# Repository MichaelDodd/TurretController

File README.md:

# TurretController
Private project for turret control

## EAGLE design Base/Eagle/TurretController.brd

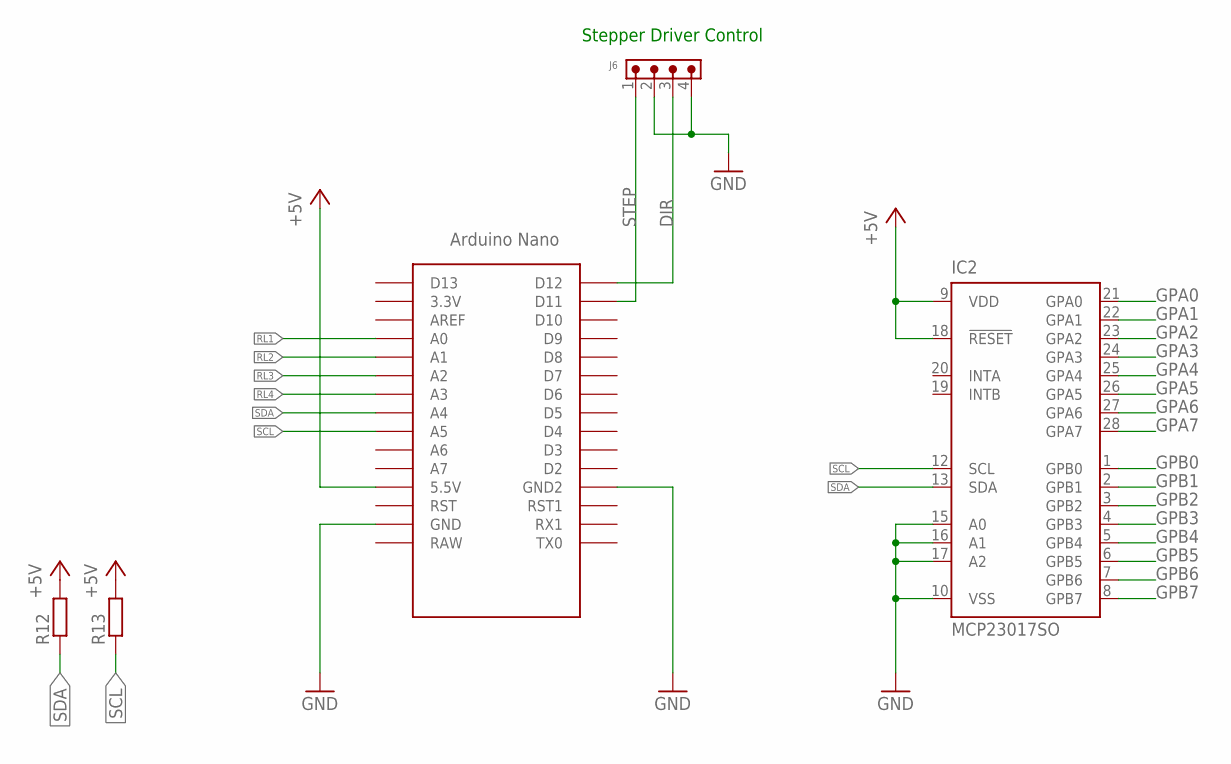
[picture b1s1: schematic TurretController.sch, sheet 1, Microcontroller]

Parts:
IC2: MCP23017SO; SO28W
J6: 691305330004
R12, R13: R-EU_R0805; R0805
U$1: NANO

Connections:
+5V: IC2.9 (VDD), IC2.18 (!RESET), R12.2, R13.2, U$1.5V (5.5V); also elsewhere on the board
DIR: J6.3, U$1.D12
GND: IC2.10 (VSS), IC2.15 (A0), IC2.16 (A1), IC2.17 (A2), J6.2, J6.4, U$1.GND, U$1.GND1 (GND2); also elsewhere on the board
GPA0: IC2.21 (GPA0); also elsewhere on the board
GPA1: IC2.22 (GPA1); also elsewhere on the board
GPA2: IC2.23 (GPA2); also elsewhere on the board
GPA3: IC2.24 (GPA3); also elsewhere on the board
GPA4: IC2.25 (GPA4); also elsewhere on the board
GPA5: IC2.26 (GPA5); also elsewhere on the board
GPA6: IC2.27 (GPA6); also elsewhere on the board
GPA7: IC2.28 (GPA7); also elsewhere on the board
GPB0: IC2.1 (GPB0); also elsewhere on the board
GPB1: IC2.2 (GPB1); also elsewhere on the board
GPB2: IC2.3 (GPB2); also elsewhere on the board
GPB3: IC2.4 (GPB3); also elsewhere on the board
GPB4: IC2.5 (GPB4); also elsewhere on the board
GPB5: IC2.6 (GPB5); also elsewhere on the board
GPB6: IC2.7 (GPB6); also elsewhere on the board
GPB7: IC2.8 (GPB7); also elsewhere on the board
RL1: U$1.A0; also elsewhere on the board
RL2: U$1.A1; also elsewhere on the board
RL3: U$1.A2; also elsewhere on the board
RL4: U$1.A3; also elsewhere on the board
SCL: IC2.12 (SCL), R13.1, U$1.A5
SDA: IC2.13 (SDA), R12.1, U$1.A4
STEP: J6.1, U$1.D11

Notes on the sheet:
Stepper Driver Control

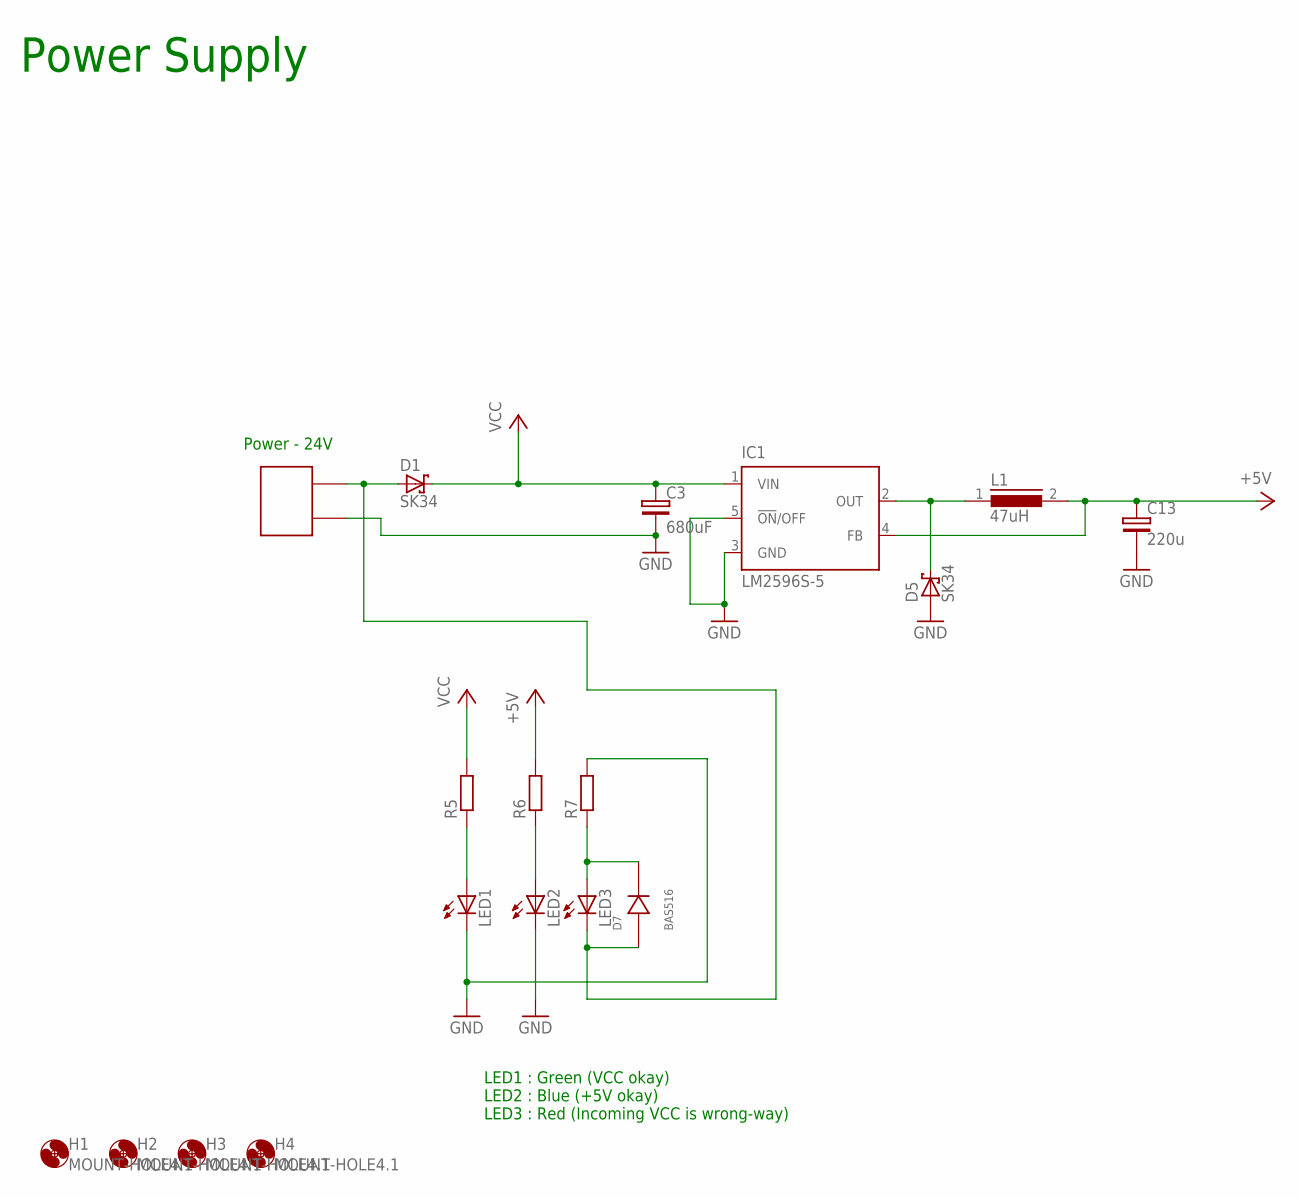
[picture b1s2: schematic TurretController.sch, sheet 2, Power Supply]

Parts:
C3: 680uF; C8.15X4X16.5
C13: 220u; PAN-PTH-8X11X3.5
CN1: 2EDG-2
D1, D5: SK34; DO214AC
D7: BAS516; SOD523
H1, H2, H3, H4: MOUNT-HOLE4.1; 4,1
IC1: LM2596S-5; TO263-5
L1: 47uH; B82476A1
LED1, LED2, LED3: LEDCHIPLED_0805; CHIPLED_0805
R5, R6, R7: R-EU_R0805; R0805

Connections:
+5V: C13.+, IC1.4 (FB), L1.2, R6.2; also elsewhere on the board
GND: C3.-, C13.-, CN1.P$1, D5.A, IC1.3 (GND), IC1.5 (!ON!/OFF), LED1.C, LED2.C, R7.2; also elsewhere on the board
unnamed: D7.C (K), LED3.A, R7.1
unnamed: D5.C, IC1.2 (OUT), L1.1
unnamed: CN1.P$2, D1.A, D7.A, LED3.C
unnamed: LED1.A, R5.1
unnamed: LED2.A, R6.1
VCC: C3.+, D1.C, IC1.1 (VIN), R5.2; also elsewhere on the board

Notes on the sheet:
LED1 : Green (VCC okay) LED2 : Blue (+5V okay) LED3 : Red (Incoming VCC is wrong-way)
Power Supply
Power - 24V

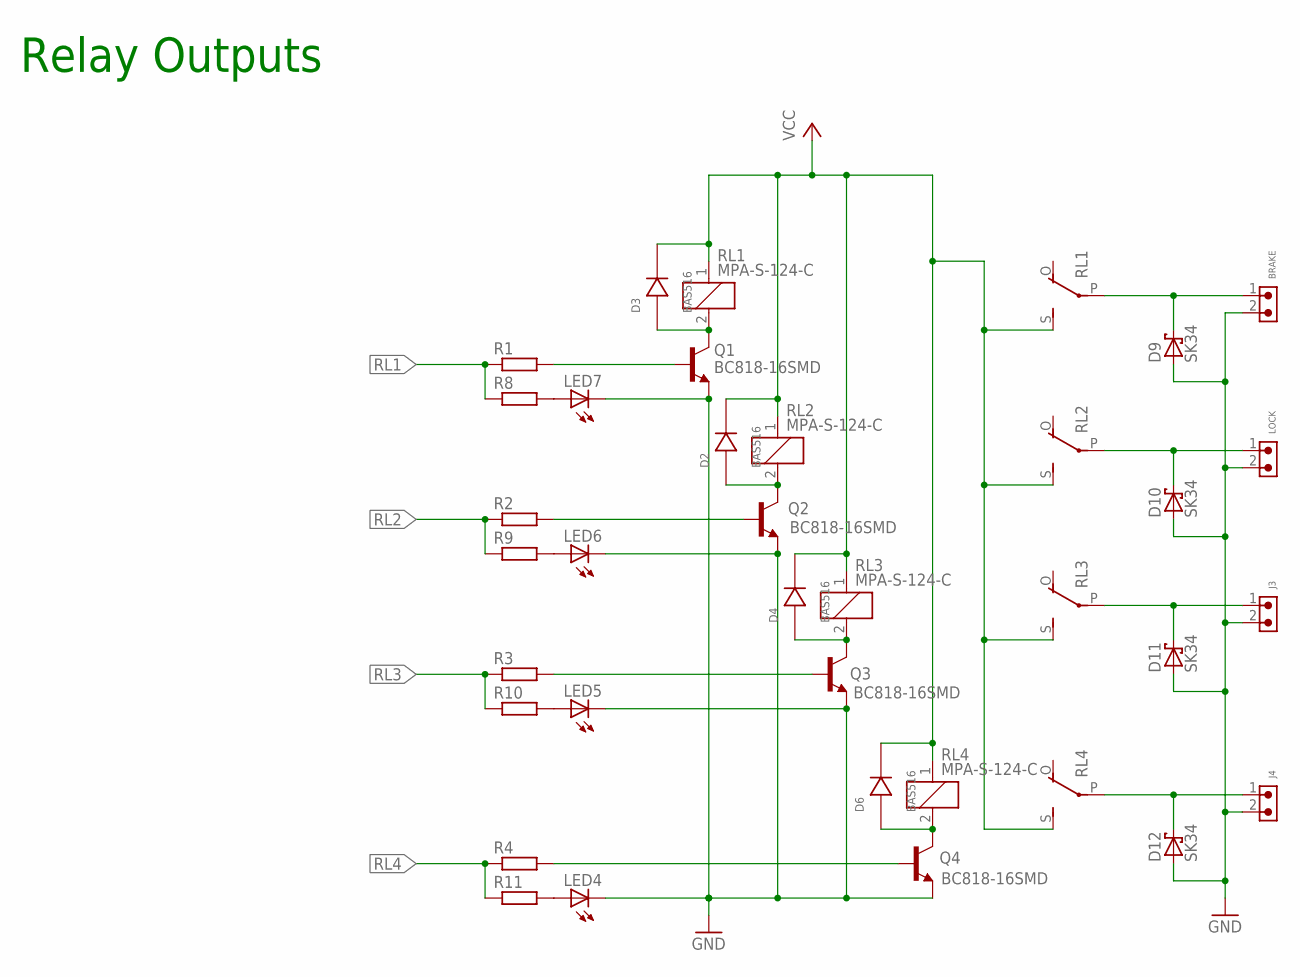
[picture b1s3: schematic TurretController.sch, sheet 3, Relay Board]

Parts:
BRAKE: 691305330002
D2, D3, D4, D6: BAS516; SOD523
D9, D10, D11, D12: SK34; DO214AC
J3, J4: 691305330002
LED4, LED5, LED6, LED7: LEDCHIPLED_0805; CHIPLED_0805
LOCK: 691305330002
Q1, Q2, Q3, Q4: BC818-16SMD; SOT23-BEC
R1, R2, R3, R4, R8, R9, R10, R11: R-EU_R0805; R0805
RL1, RL2, RL3, RL4: MPA-S-124-C; G5LE

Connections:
GND: BRAKE.2, D9.A, D10.A, D11.A, D12.A, J3.2, J4.2, LED4.C, LED5.C, LED6.C, LED7.C, LOCK.2, Q1.E, Q2.E, Q3.E, Q4.E; also elsewhere on the board
unnamed: D12.C, J4.1, RL4.P
unnamed: D11.C, J3.1, RL3.P
unnamed: D10.C, LOCK.1, RL2.P
unnamed: BRAKE.1, D9.C, RL1.P
unnamed: D2.A, Q2.C, RL2.2
unnamed: LED4.A, R11.2
unnamed: D4.A, Q3.C, RL3.2
unnamed: D3.A, Q1.C, RL1.2
unnamed: D6.A, Q4.C, RL4.2
unnamed: Q1.B, R1.2
unnamed: Q2.B, R2.2
unnamed: Q3.B, R3.2
unnamed: Q4.B, R4.2
unnamed: LED5.A, R10.2
unnamed: LED6.A, R9.2
unnamed: LED7.A, R8.2
RL1: R1.1, R8.1; also elsewhere on the board
RL2: R2.1, R9.1; also elsewhere on the board
RL3: R3.1, R10.1; also elsewhere on the board
RL4: R4.1, R11.1; also elsewhere on the board
VCC: D2.C (K), D3.C (K), D4.C (K), D6.C (K), RL1.1, RL1.S, RL2.1, RL2.S, RL3.1, RL3.S, RL4.1, RL4.S; also elsewhere on the board

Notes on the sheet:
Relay Outputs

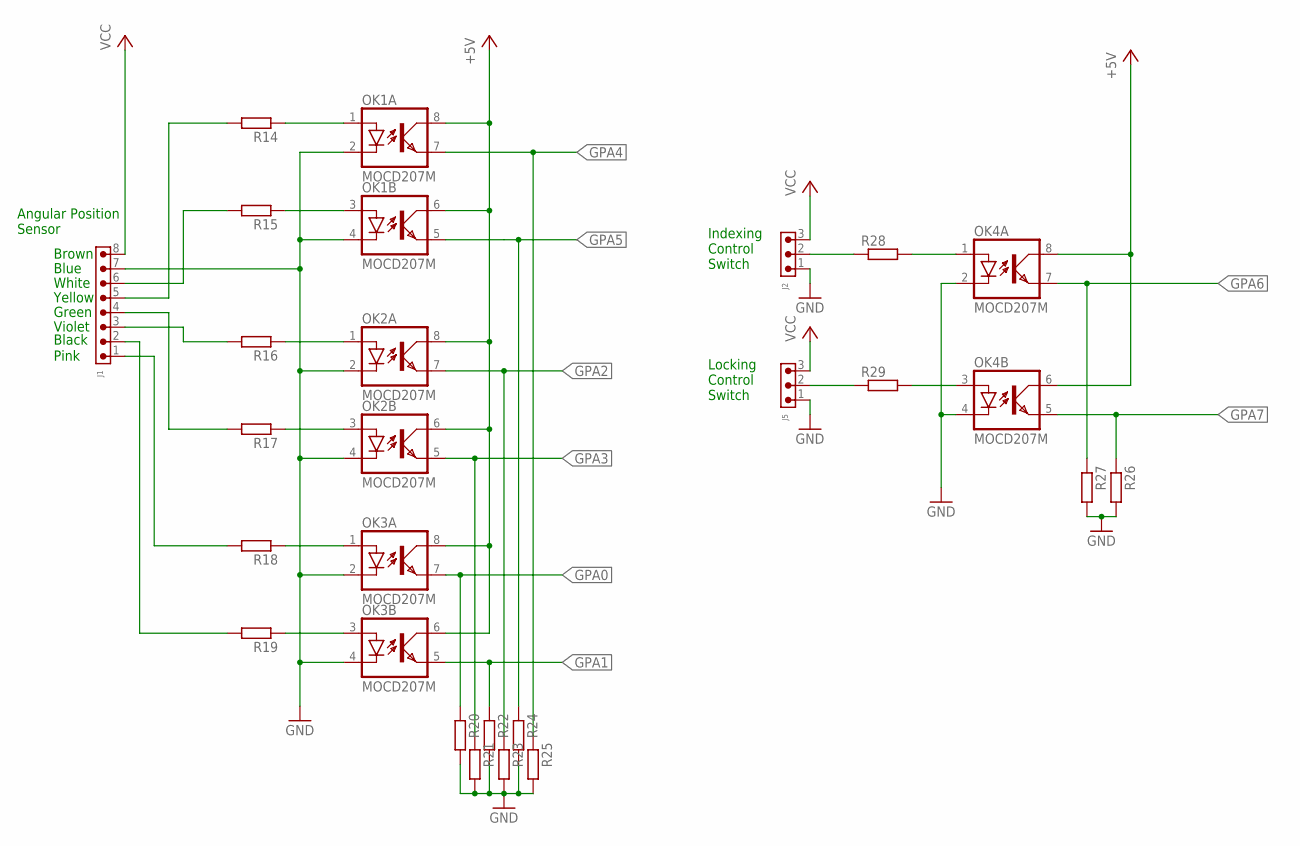
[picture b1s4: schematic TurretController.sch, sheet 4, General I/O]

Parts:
J1: 691305330008
J2, J5: 691305330003
OK1, OK2, OK3, OK4: MOCD207M; SOIC08-FAIRCHILD
R14, R15, R16, R17, R18, R19, R20, R21, R22, R23, R24, R25, R26, R27, R28, R29: R-EU_R0805; R0805

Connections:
+5V: OK1.6 (COL), OK1.8 (COL), OK2.6 (COL), OK2.8 (COL), OK3.6 (COL), OK3.8 (COL), OK4.6 (COL), OK4.8 (COL); also elsewhere on the board
GND: J1.7, J2.1, J5.1, OK1.2 (C), OK1.4 (C), OK2.2 (C), OK2.4 (C), OK3.2 (C), OK3.4 (C), OK4.2 (C), OK4.4 (C), R20.2, R21.2, R22.2, R23.2, R24.2, R25.2, R26.2, R27.2; also elsewhere on the board
GPA0: OK3.7 (EMIT), R20.1; also elsewhere on the board
GPA1: OK3.5 (EMIT), R22.1; also elsewhere on the board
GPA2: OK2.7 (EMIT), R23.1; also elsewhere on the board
GPA3: OK2.5 (EMIT), R21.1; also elsewhere on the board
GPA4: OK1.7 (EMIT), R25.1; also elsewhere on the board
GPA5: OK1.5 (EMIT), R24.1; also elsewhere on the board
GPA6: OK4.7 (EMIT), R27.1; also elsewhere on the board
GPA7: OK4.5 (EMIT), R26.1; also elsewhere on the board
unnamed: J1.1, R18.2
unnamed: J2.2, R28.1
unnamed: OK4.1 (A), R28.2
unnamed: OK4.3 (A), R29.2
unnamed: J5.2, R29.1
unnamed: J1.3, R16.2
unnamed: J1.4, R17.2
unnamed: J1.6, R15.2
unnamed: J1.5, R14.2
unnamed: OK2.3 (A), R17.1
unnamed: OK1.1 (A), R14.1
unnamed: OK1.3 (A), R15.1
unnamed: OK2.1 (A), R16.1
unnamed: OK3.1 (A), R18.1
unnamed: OK3.3 (A), R19.1
unnamed: J1.2, R19.2
VCC: J1.8, J2.3, J5.3; also elsewhere on the board

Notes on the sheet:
Angular Position Sensor
Indexing Control Switch
Locking Control Switch
Brown
Blue
White
Yellow
Green
Violet
Black
Pink

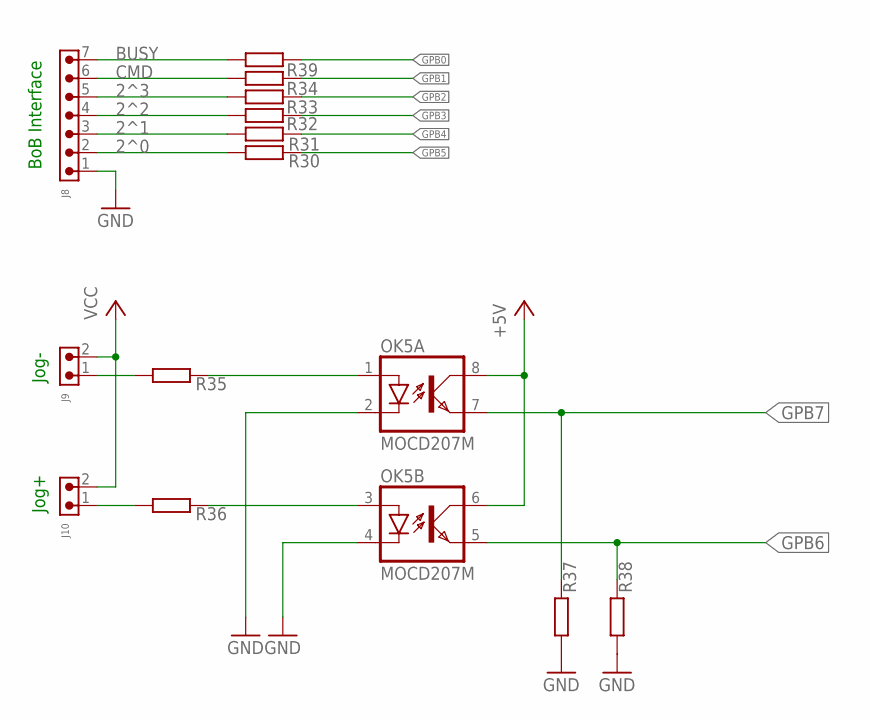
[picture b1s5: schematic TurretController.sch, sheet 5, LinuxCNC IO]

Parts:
J8: 691305330007
J9, J10: 691305330002
OK5: MOCD207M; SOIC08-FAIRCHILD
R30, R31, R32, R33, R34, R35, R36, R37, R38, R39: R-EU_R0805; R0805

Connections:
2^0: J8.2, R30.2
2^1: J8.3, R31.2
2^2: J8.4, R32.2
2^3: J8.5, R33.2
+5V: OK5.6 (COL), OK5.8 (COL); also elsewhere on the board
BUSY: J8.7, R39.2
CMD: J8.6, R34.2
GND: J8.1, OK5.2 (C), OK5.4 (C), R37.2, R38.2; also elsewhere on the board
GPB0: R39.1; also elsewhere on the board
GPB1: R34.1; also elsewhere on the board
GPB2: R33.1; also elsewhere on the board
GPB3: R32.1; also elsewhere on the board
GPB4: R31.1; also elsewhere on the board
GPB5: R30.1; also elsewhere on the board
GPB6: OK5.5 (EMIT), R38.1; also elsewhere on the board
GPB7: OK5.7 (EMIT), R37.1; also elsewhere on the board
unnamed: J9.1, R35.2
unnamed: J10.1, R36.2
unnamed: OK5.3 (A), R36.1
unnamed: OK5.1 (A), R35.1
VCC: J9.2, J10.2; also elsewhere on the board

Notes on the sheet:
BoB Interface
Jog-
Jog+

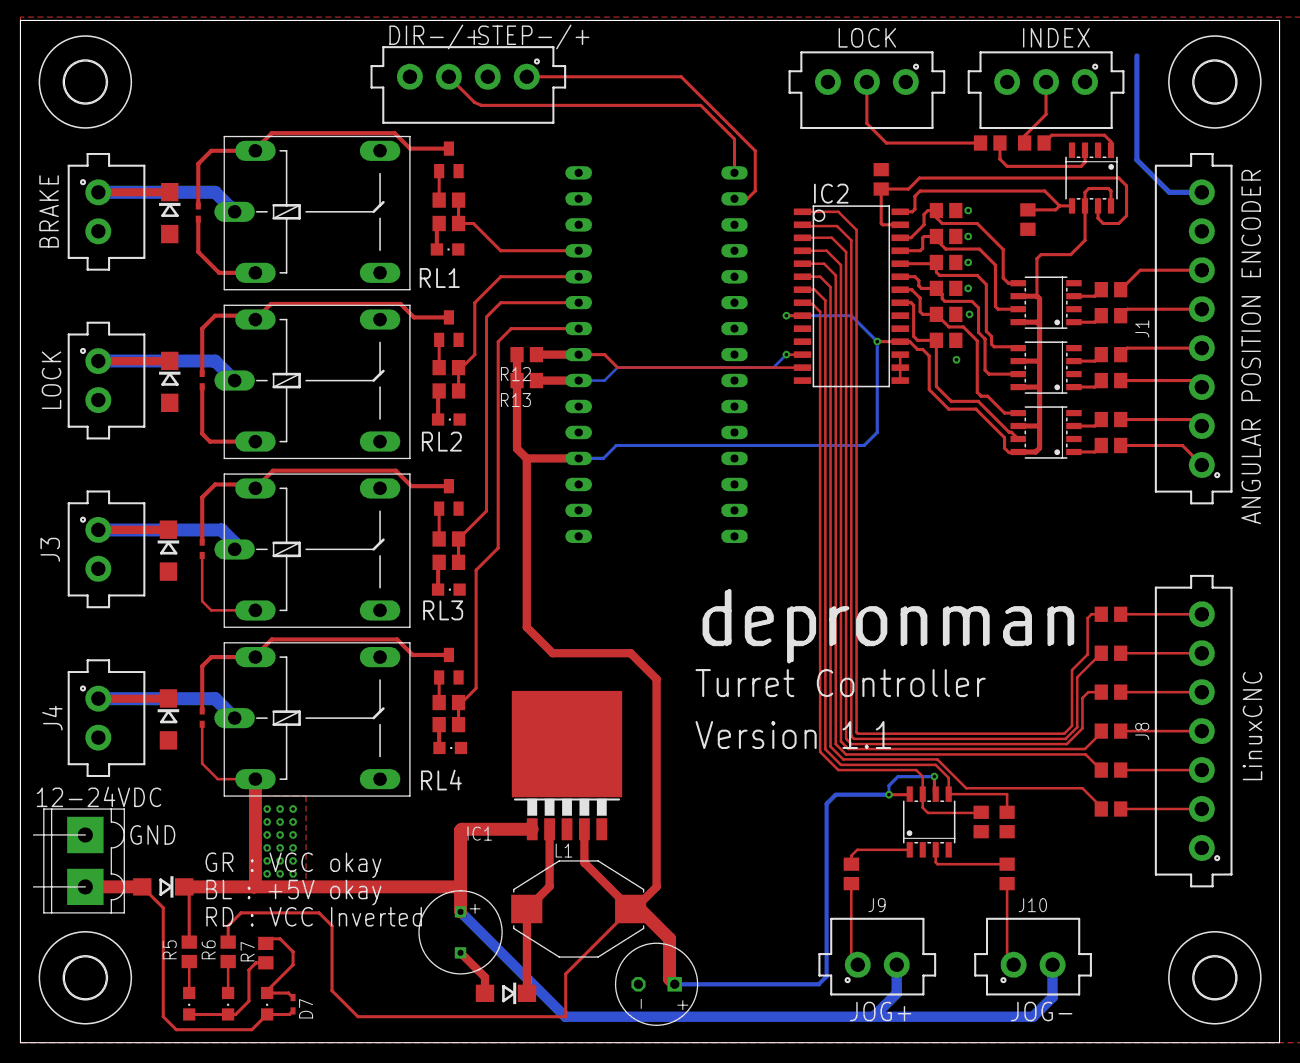
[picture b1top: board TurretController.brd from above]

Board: 2 copper layers, 123.2 x 100.0 mm, 92 parts (0 on the bottom side), 74 nets.

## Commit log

2022-02-21 Create temp
2022-02-21 Create test
2022-02-21 Update TurretCtrl.cpp
    Original version 1.0 baseline
2022-02-21 Update TurretCtrl.cpp
    Fix the logic for the optimal tool-move
2022-02-26 Changes to repo structure
2022-02-26 First corrections to board, addition of protection diodes
